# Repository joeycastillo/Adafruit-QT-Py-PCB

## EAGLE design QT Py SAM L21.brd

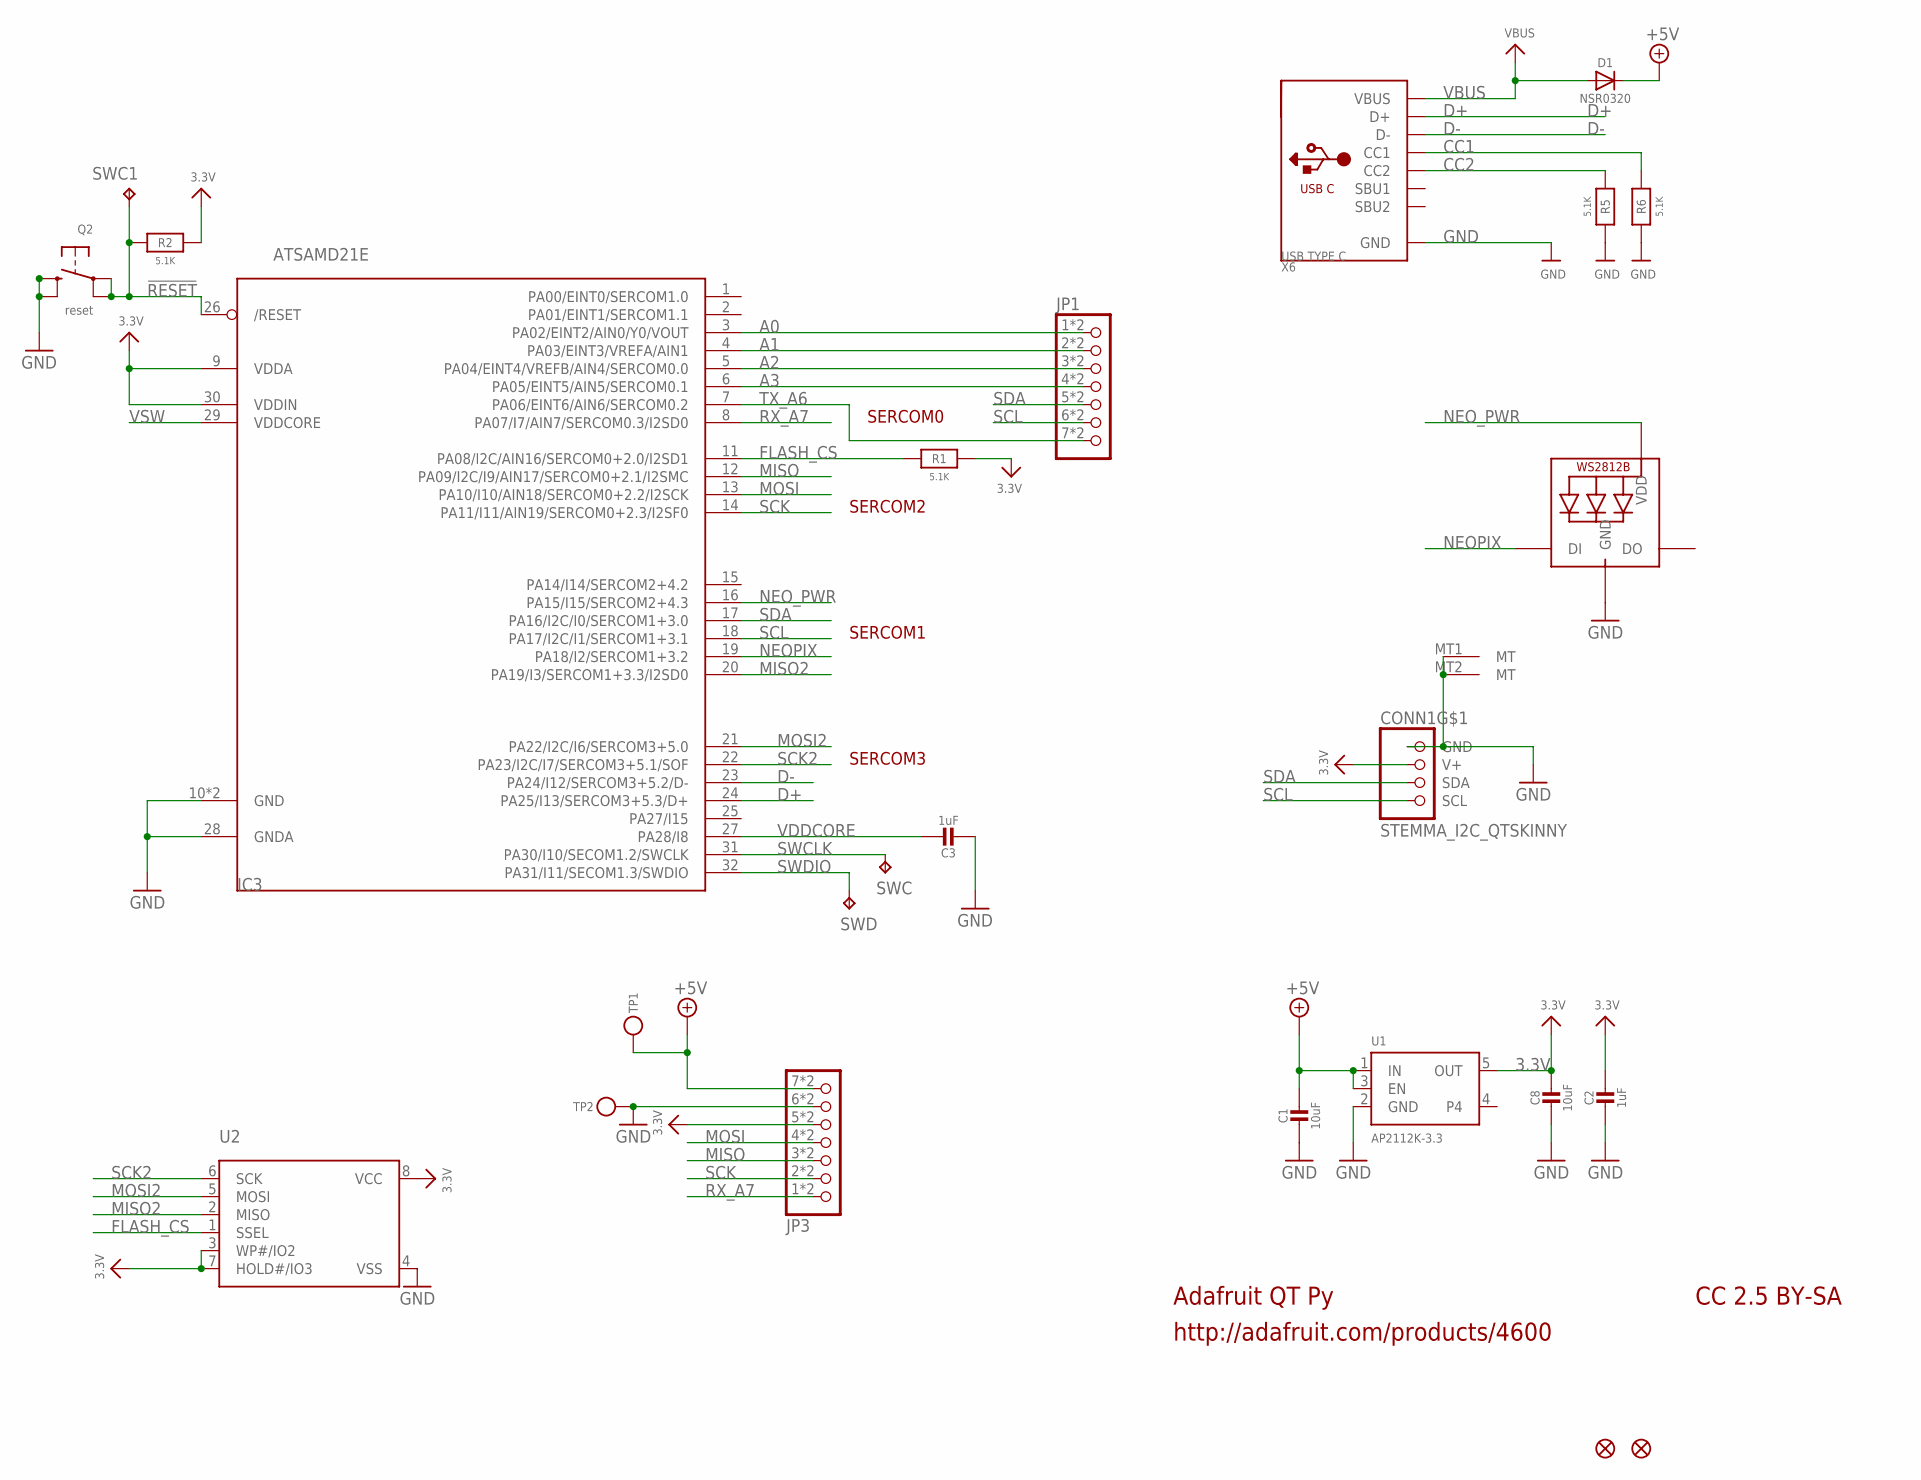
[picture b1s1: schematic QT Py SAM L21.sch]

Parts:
C1, C8: 10uF; _0805MP
C2, C3: 1uF; _0402NO
CONN1: STEMMA_I2C_QTSKINNY; JST_SH4_SKINNY
D1: NSR0320; SOD-323_MINI
IC3: ATSAMD21E; QFN32_5MM
JP1, JP3: HEADER-1X7_CASTEL; 1X07_CASTEL
LED1: WS2812B_SK6805_1515; SK6805_1515
Q2: reset; BTN_KMR2_4.6X2.8
R1, R2, R5, R6: 5.1K; _0402NO
SWC, SWC1: TPB1,27; B1,27
SWD: TPB1,27; B1,27
TP1, TP2: TESTPOINT_1X3; TESTPOINT_RECT_1X3MM
U1: AP2112K-3.3; SOT23-5
U2: SPIFLASH_8PIN; SOIC8_150MIL
U$6, U$8: FIDUCIAL_1MM
X6: USB TYPE C; USB_C_CUSB31-CFM2AX-01-X

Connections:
3.3V: C2.1, C8.1, CONN1.2 (V+), IC3.9 (VDDA), IC3.30 (VDDIN), JP3.5, JP3.5C (5), R1.1, R2.1, U1.5 (OUT), U2.3 (WP#/IO2), U2.7 (HOLD#/IO3), U2.8 (VCC)
!RESET: IC3.26 (/RESET), Q2.A, Q2.A' (P1), R2.2, SWC1.TP
+5V: C1.1, D1.C, JP3.7, JP3.7C (7), TP1.P$1, U1.1 (IN), U1.3 (EN)
A0: IC3.3 (PA02/EINT2/AIN0/Y0/VOUT), JP1.1, JP1.1C (1)
A1: IC3.4 (PA03/EINT3/VREFA/AIN1), JP1.2, JP1.2C (2)
A2: IC3.5 (PA04/EINT4/VREFB/AIN4/SERCOM0.0), JP1.3, JP1.3C (3)
A3: IC3.6 (PA05/EINT5/AIN5/SERCOM0.1), JP1.4, JP1.4C (4)
CC1: R6.2, X6.A5 (CC1)
CC2: R5.2, X6.B5 (CC2)
D+: IC3.24 (PA25/I13/SERCOM3+5.3/D+), X6.A6 (D+), X6.B6 (D+)
D-: IC3.23 (PA24/I12/SERCOM3+5.2/D-), X6.A7 (D-), X6.B7 (D-)
FLASH_CS: IC3.11 (PA08/I2C/AIN16/SERCOM0+2.0/I2SD1), R1.2, U2.1 (SSEL)
GND: C1.2, C2.2, C3.2, C8.2, CONN1.1 (GND), CONN1.MT1 (MT), CONN1.MT2 (MT), IC3.10 (GND), IC3.28 (GNDA), IC3.33 (GND), JP3.6, JP3.6C (6), LED1.4 (GND), Q2.B (S), Q2.B' (S1), R5.1, R6.1, TP2.P$1, U1.2 (GND), U2.4 (VSS), X6.A1B12 (GND), X6.B1A12 (GND)
MISO: IC3.12 (PA09/I2C/I9/AIN17/SERCOM0+2.1/I2SMC), JP3.3, JP3.3C (3)
MISO2: IC3.20 (PA19/I3/SERCOM1+3.3/I2SD0), U2.2 (MISO)
MOSI: IC3.13 (PA10/I10/AIN18/SERCOM0+2.2/I2SCK), JP3.4, JP3.4C (4)
MOSI2: IC3.21 (PA22/I2C/I6/SERCOM3+5.0), U2.5 (MOSI)
NEOPIX: IC3.19 (PA18/I2/SERCOM1+3.2), LED1.1 (DI)
NEO_PWR: IC3.16 (PA15/I15/SERCOM2+4.3), LED1.2 (VDD)
RX_A7: IC3.8 (PA07/I7/AIN7/SERCOM0.3/I2SD0), JP3.1, JP3.1C (1)
SCK: IC3.14 (PA11/I11/AIN19/SERCOM0+2.3/I2SF0), JP3.2, JP3.2C (2)
SCK2: IC3.22 (PA23/I2C/I7/SERCOM3+5.1/SOF), U2.6 (SCK)
SCL: CONN1.4 (SCL), IC3.18 (PA17/I2C/I1/SERCOM1+3.1), JP1.6, JP1.6C (6)
SDA: CONN1.3 (SDA), IC3.17 (PA16/I2C/I0/SERCOM1+3.0), JP1.5, JP1.5C (5)
SWCLK: IC3.31 (PA30/I10/SECOM1.2/SWCLK), SWC.TP
SWDIO: IC3.32 (PA31/I11/SECOM1.3/SWDIO), SWD.TP
TX_A6: IC3.7 (PA06/EINT6/AIN6/SERCOM0.2), JP1.7, JP1.7C (7)
VBUS: D1.A, X6.A4B9 (VBUS), X6.B4A9 (VBUS)
VDDCORE: C3.1, IC3.27 (PA28/I8)
VSW: IC3.29 (VDDCORE)

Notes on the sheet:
Adafruit QT Py
http://adafruit.com/products/4600
CC 2.5 BY-SA
SERCOM0
SERCOM1
SERCOM2
SERCOM3

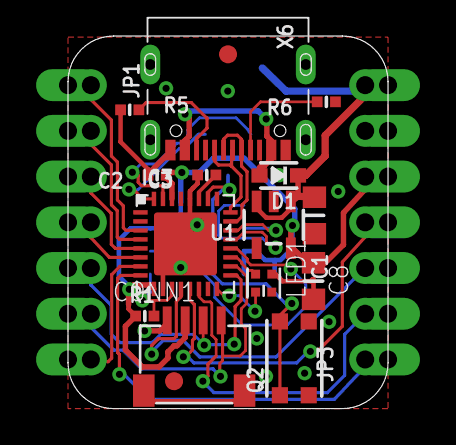
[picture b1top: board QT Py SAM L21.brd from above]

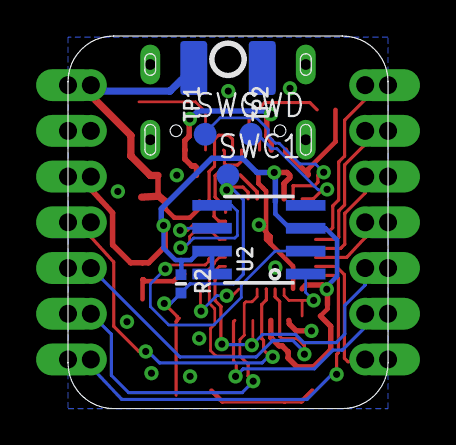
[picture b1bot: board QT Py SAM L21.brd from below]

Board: 2 copper layers, 17.8 x 20.7 mm, 28 parts (9 on the bottom side), 29 nets.

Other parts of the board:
U$11: QTPY_BOT
U$12: PCBFEAT-REV-040
U$13: QTPY_TOP

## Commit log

2022-07-20 Tweaks to support SAM L21

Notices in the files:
parts and their libraries:
microbuilder: This work is placed in the public domain, and may be freely used for commercial and non-commercial work with the following conditions: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
